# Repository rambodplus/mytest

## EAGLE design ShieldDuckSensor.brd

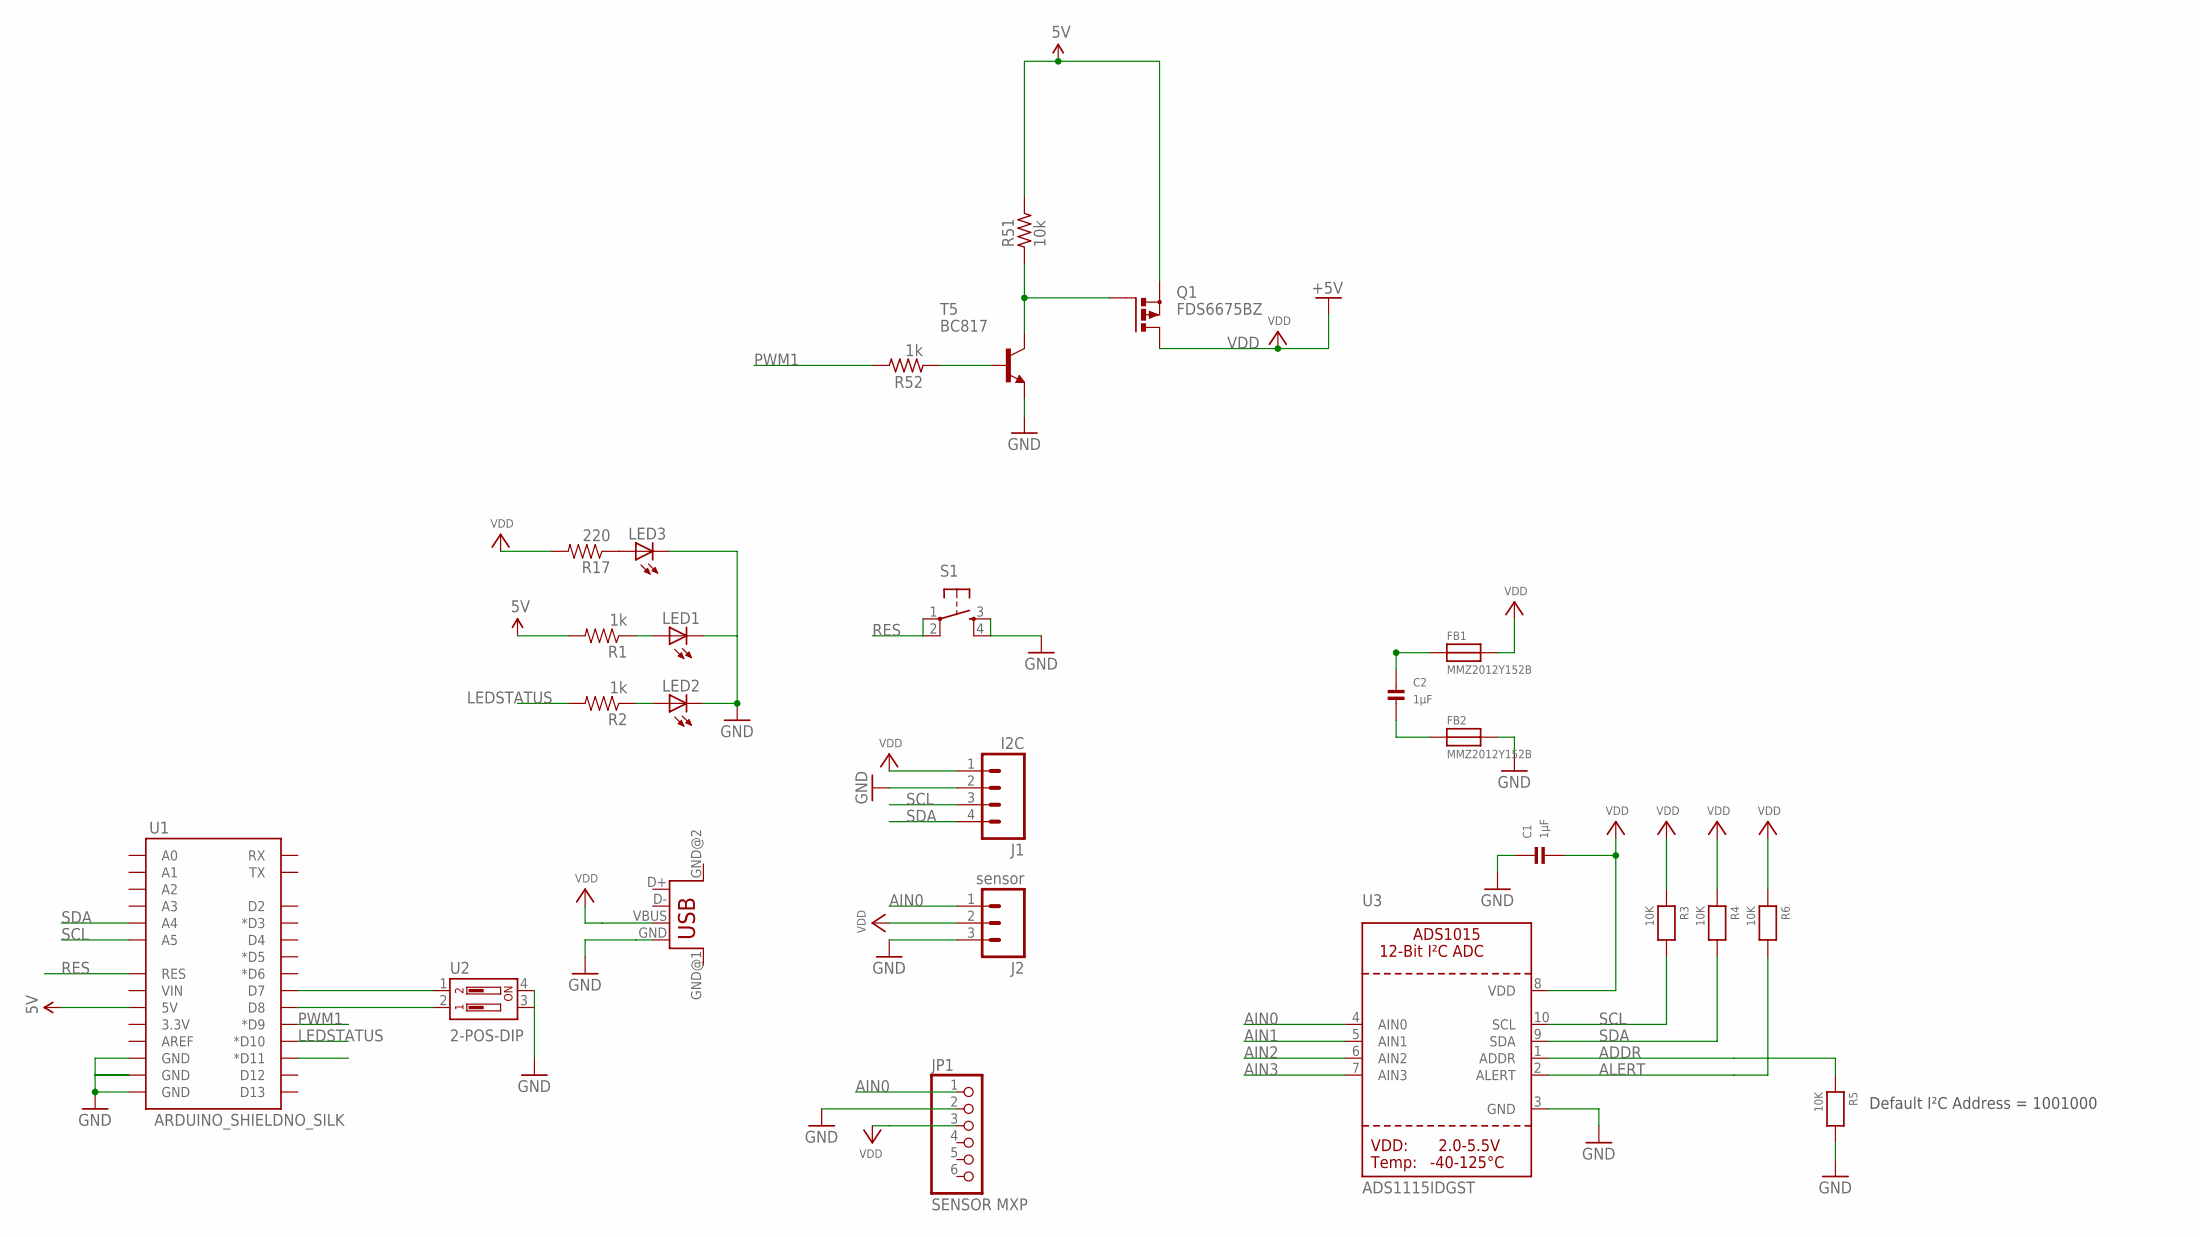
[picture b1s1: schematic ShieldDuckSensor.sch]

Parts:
C1, C2: 1µF; 0805
FB1, FB2: MMZ2012Y152B; 0805
J1: I2C; 1X04
J2: sensor; 1X03
JP1: SENSOR MXP; 1X06-BIG
LED1, LED2, LED3: LED3MM
Q1: FDS6675BZ; SO-08
R1, R2: 1k; 0805
R3, R4, R5, R6: 10K; 0805
R17: 220; 0805
R51: 10k; R0805
R52: 1k; R0805
S1: TAC_SWITCHPTH; TACTILE-PTH
T5: BC817; SOT23-BEC
U1: ARDUINO_SHIELDNO_SILK; DUEMILANOVE_VIAS
U2: 2-POS-DIP; 209-2LPST
U3: ADS1115IDGST; MSOP10
U$1: USB; USB-FEMALE-A-PTH

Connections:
5V: Q1.1 (S), Q1.2 (S), Q1.3 (S), R1.2, R51.2, U1.5V
ADDR: R5.1, U3.1 (ADDR)
AIN0: J2.1, JP1.1, U3.4 (AIN0)
AIN1: U3.5 (AIN1)
AIN2: U3.6 (AIN2)
AIN3: U3.7 (AIN3)
ALERT: R6.2, U3.2 (ALERT)
GND: C1.1, FB2.2, J1.2, J2.3, JP1.2, LED1.K (C), LED2.K (C), LED3.K (C), R5.2, S1.3, S1.4, T5.E, U1.GND@0 (GND), U1.GND@1 (GND), U1.GND@2 (GND), U2.3, U2.4, U3.3 (GND), U$1.GND
LEDSTATUS: R2.2, U1.D10 (*D10)
unnamed: LED1.A, R1.1
unnamed: U1.D7, U2.1
unnamed: U1.D8, U2.2
unnamed: LED2.A, R2.1
unnamed: C2.2, FB2.1
unnamed: C2.1, FB1.1
unnamed: LED3.A, R17.1
unnamed: Q1.4 (G), R51.1, T5.C
unnamed: R52.1, T5.B
PWM1: R52.2, U1.D9 (*D9)
RES: S1.1, S1.2, U1.RES
SCL: J1.3, R3.2, U1.A5, U3.10 (SCL)
SDA: J1.4, R4.2, U1.A4, U3.9 (SDA)
VDD: C1.2, FB1.2, J1.1, J2.2, JP1.3, Q1.5 (D), Q1.6 (D), Q1.7 (D), Q1.8 (D), R3.1, R4.1, R6.1, R17.2, U3.8 (VDD), U$1.VBUS

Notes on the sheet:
Default I²C Address = 1001000

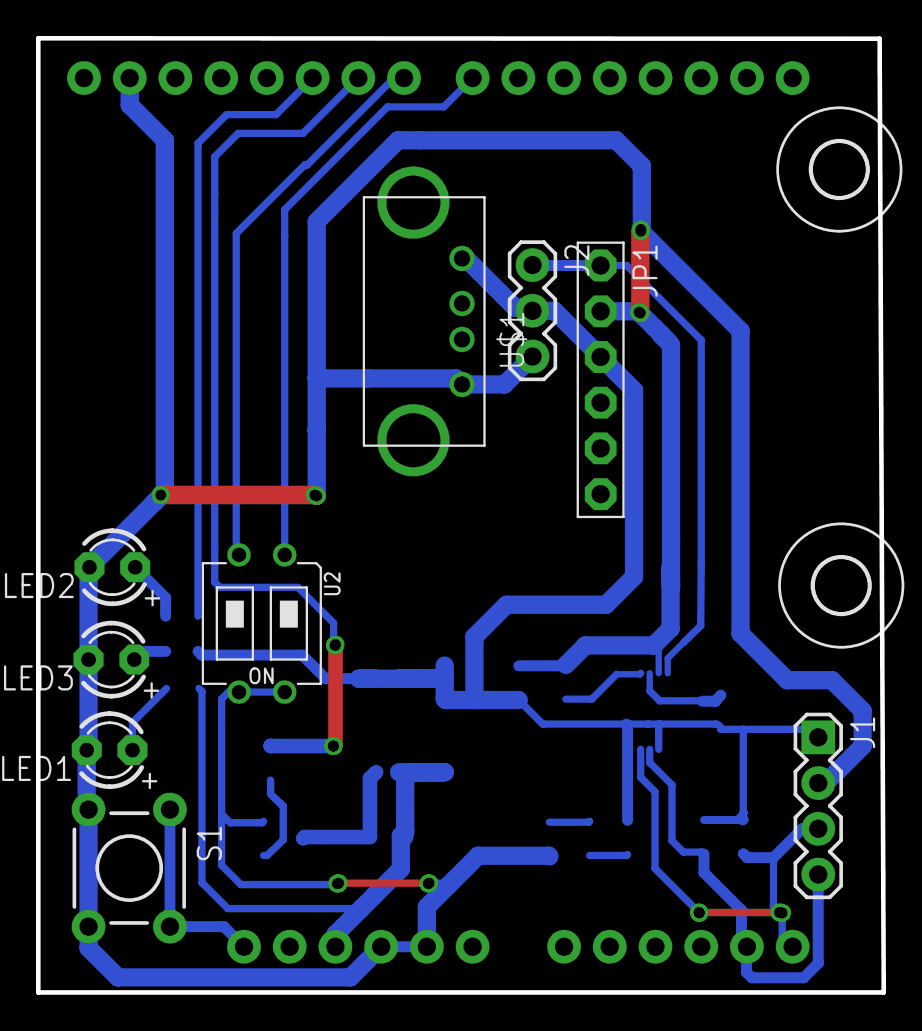
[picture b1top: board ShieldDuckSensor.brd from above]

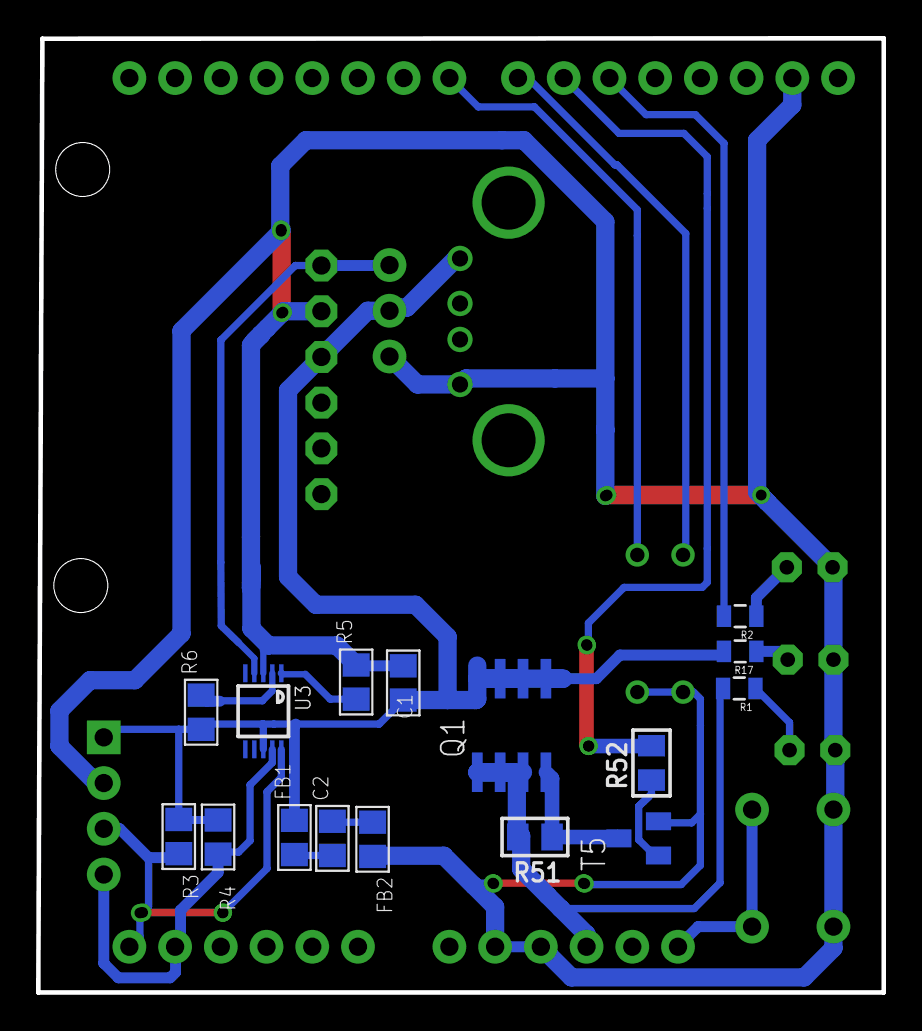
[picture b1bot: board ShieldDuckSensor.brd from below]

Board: 2 copper layers, 47.0 x 53.0 mm, 28 parts (16 on the bottom side), 20 nets.

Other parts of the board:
U$3, U$6: 3,0

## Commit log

2016-06-22 re new file
2016-06-22 Add note file.
2016-06-22 add neame
2016-06-22 Add another line.

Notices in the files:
parts and their libraries:
SparkFun-Boards: Licensing: Creative Commons ShareAlike 4.0 International - https://creativecommons.org/licenses/by-sa/4.0
SparkFun-Resistors: Licensing: CC v3.0 Share-Alike You are welcome to use this library for commercial purposes.
